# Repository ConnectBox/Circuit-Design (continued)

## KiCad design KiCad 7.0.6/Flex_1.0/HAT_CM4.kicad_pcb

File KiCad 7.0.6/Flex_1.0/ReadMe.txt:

Re: Saving project with new name (ie file names change)

From: https://forum.kicad.info/t/how-to-clone-a-project/3878/12

--------------------
I did an experiment to see the minimum set of files I needed to rebuild a design. Here they are:

myproj.pro : The project file that ties everything together.
myproj.sch : The Schematic file (or files in the case of a hierarchical design).
myproj.kicad_pcb : The PCB layout. It also contains the footprint for every component used in the PCB layout.
myproj-cache.lib : This contains the schematic symbol for every component used in the schematic file. It gets generated whenever you save the schematic or project.

So all you need are those four files. If the shared libraries with the component footprints and/or schematic symbols are missing, then KiCad seems to get the information it needs from these files. These files may also be given priority even if the shared libraries are present; I don’t know.
-------------------

(NOTE: In KiCAD 5.99 the myproj-cache.lib file is missing... but it doesn't seem to be needed as saving the other files in a new folder and opening the project with KiCAD seems to work fine. There is a file "fp-info-cache" that I DIDN'T copy into the new project directory... but KiCAD seems to have created a new fp-info-cache when I opened the project.) 

From that same link we get the following on using the tool "git":

------------------
You probably don’t want to hear this (most people don’t), but git easily does this for you. (Note that I’m talking about git, not Github.)

In your kicad project directory, just do git init. This creates a repository that stores all your project versions.

Add the project files you want to keep track of. For kicad, there’s really only three you need: git add myproj.pro myproj.sch myproj.kicad_pcb.

Store the current state of your project: git commit -a -m "Some message about this version".

That’s all you need to do to setup versioning. Then whenever you have a version you want to save, run the command git commit -a -m "A message about this version". If you also want to give the snapshot an easy-to-remember name, you can use the command git tag my_version_tag. Then if you ever want to return to that version, use the command git checkout my_version_tag. And if you want to see the history of your project, use git log.
-----------------

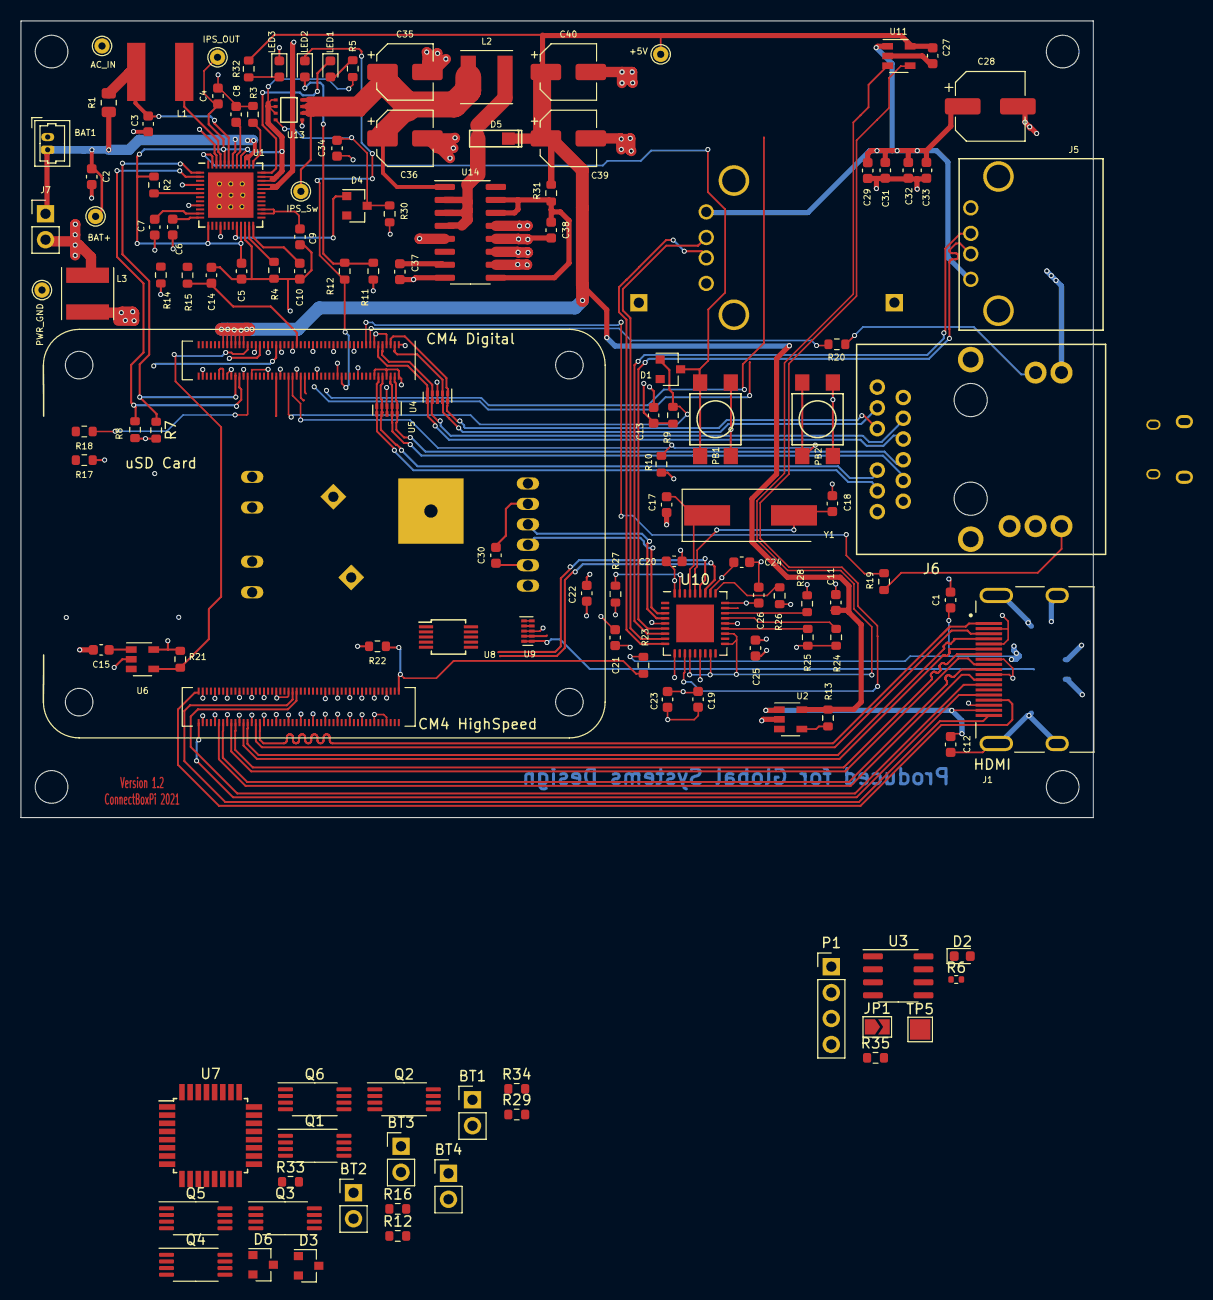
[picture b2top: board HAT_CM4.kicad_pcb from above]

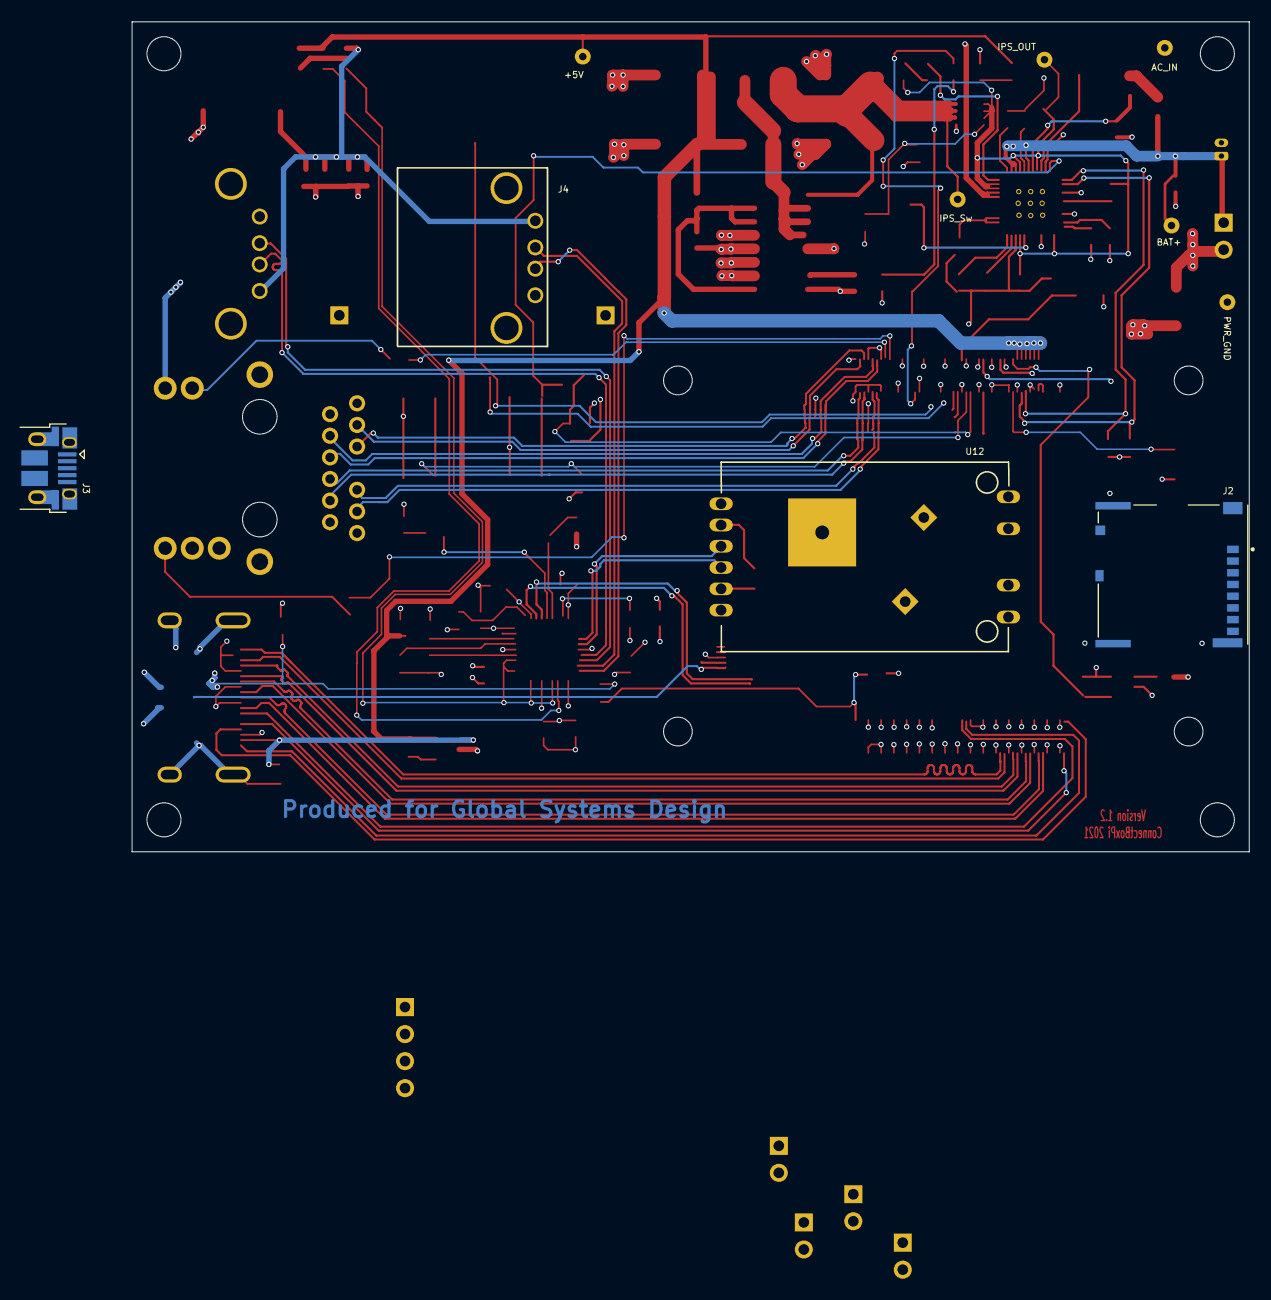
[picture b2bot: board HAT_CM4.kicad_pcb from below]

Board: 4 copper layers, 105.0 x 78.0 mm, 132 parts (4 on the bottom side), 115 nets.

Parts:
BAT1: Molex PicoBlade 53047-0210; Molex PicoBlade 53047-0210 - (swapped pins)
BT1, BT2, BT3, BT4: Battery_Cell; PinHeader_1x02_P2.54mm_Vertical
C1, C30, C34: 22uF; C_0603_1608Metric
C2, C3, C4, C5, C14, C15, C19, C20, C27, C29, C31, C32, C33: 10uF; C_0603_1608Metric
C6, C7, C8: 4.7uF; C_0603_1608Metric
C9, C10, C13: 1uF; C_0603_1608Metric
C11, C12, C21, C22, C23, C24, C25, C26, C38: 0.1uf; C_0603_1608Metric
C17, C18: 27pF; C_0603_1608Metric
C28: 100uF; CP_Elec_6.3x4.5
C35, C36, C39, C40: 150uf; CP_Elec_5x3
C37: 0.22uf; C_0603_1608Metric
D1, D3, D4, D6: MMBD914; D_SOT-23_ANK
D2: LED Green; LED_0603_1608Metric
D5: NRVTS260ESFT1G; SOD-123FL
J1: 690-019-298-412; EDAC 690-019-298-412
J2: Micro_SD_Card_Det; SDCARD_MOLEX_503398-1892
J3: USB_OTG; USB_Micro-B_EDAC_UCON00686
J4, J5: USB_A
J6: MagJack-L829-1J1T-JM; MagJack L829-1J1T-JM
J7: Conn_01x02_Female; PinHeader_1x02_P2.54mm_Vertical
JP1: SolderJumper_2_Open; SolderJumper-2_P1.3mm_Open_TrianglePad1.0x1.5mm
L1: 4.7 uH; INDUCTOR_SMD_6x6-1
L2: 1.0 uH; L_Taiyo-Yuden_MD-5050
L3: 1.5 uH; L_Taiyo-Yuden_NR-50xx
LED1: Red; LED_0603_1608Metric
LED2: Amber; LED_0603_1608Metric
LED3: Green; LED_0603_1608Metric
Module1: ComputeModule4; Raspberry-Pi-4-Compute-Module
P1: Conn_01x04; PinHeader_1x04_P2.54mm_Vertical
PB1, PB2: SPST-PUSH; SW-TL3305
Q1, Q2, Q3, Q4, Q5, Q6: 8205A; TSSOP-8_4.4x3mm_P0.65mm
R1: 0.03 ohm; R_0805_2012Metric
R2, R9, R10, R12, R29, R34, R35: 10K; R_0603_1608Metric
R3: 100; R_0603_1608Metric
R4: 200K; R_0603_1608Metric
R5: 1.8K; R_0603_1608Metric
R6: 1k; R_0402_1005Metric
R7, R8, R16, R22, R23, R33: 2.2K; R_0603_1608Metric
R11, R12#2, R15, R32: 1K; R_0603_1608Metric
R13, R21, R27: 12K; R_0603_1608Metric
R14: 51K; R_0603_1608Metric
R17, R18: nf; R_0603_1608Metric
R19, R20: 470; R_0603_1608Metric
R24, R25, R26, R28: 36.0K; R_0603_1608Metric
R30: 220K; R_0603_1608Metric
R31: 2.0; R_0603_1608Metric
TP1: Pwr_Gnd; TestPoint_THTPad_D1.5mm_Drill0.7mm
TP2: AC_IN; TestPoint_THTPad_D1.5mm_Drill0.7mm
TP3: Bat+; TestPoint_THTPad_D1.5mm_Drill0.7mm
TP4: IPS; TestPoint_THTPad_D1.5mm_Drill0.7mm
TP5: TestPoint; TestPoint_Pad_2.0x2.0mm
TP7: IPS_Sw; TestPoint_THTPad_D1.5mm_Drill0.7mm
TP8: 5V; TestPoint_THTPad_D1.5mm_Drill0.7mm
U1: AXP209; UQFN-48-1EP_6x6mm_Pitch0.4mm_75
U2: RT9742SNGV; SOT-23-5
U3: AT24CS01-SSHM; SOIC-8_3.9x4.9mm_P1.27mm
U4, U5, U9: TPD4EUSB30; USON-10_2.5x1.0mm_P0.5mm
U6, U11: RT9742ANGJ5F; SOT-23-5
U7: ATtiny88-AU; TQFP-32_7x7mm_P0.8mm
U8: FSUSB42MUX; MSOP-10_3x3mm_P0.5mm
U10: USB2514B-I/M2; QFN-36-1EP_6x6mm_P0.5mm_EP3.7x3.7mm
U12: HC-R8812AF1; HC-R8812AU2-th-1
U13: DML10M8LDS-13
U14: MAX1709ESE; SOP-16_3.9x9.9mm_P1.27mm
Y1: 24MHz; Crystal_SMD_HC49-SD

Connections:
+3.3v: C13.1, C19.1, C20.1, C21.1, C22.1, C23.1, C24.1, C25.1, C26.1, C30.1, J6.14 (LEDY_A), J6.16 (COM), Module1.78 (GPIO_VREF(1.8v/3.3v_Input)), Module1.84 (+3.3v_(Output)), Module1.86 (+3.3v_(Output)), R7.2, R8.2, R9.2, R10.2, R11.1, R14.1, R17.1, R21.2, U6.5 (VIN), U8.1 (VCC), U10.5 (VDDA33), U10.10 (VDDA33), U10.15 (VDD33), U10.23 (VDD33), U10.27 (VBUS_DET), U10.29 (VDDA33), U10.36 (VDDA33), U12.1 (PDN), U12.2 (3.3V)
+5v: C11.1, C27.1, C39.1, C40.1, D2.2 (A), D5.1 (K), D6.2 (A), JP1.1 (A), Module1.77 (+5v_(Input)), Module1.79 (+5v_(Input)), Module1.81 (+5v_(Input)), Module1.83 (+5v_(Input)), Module1.85 (+5v_(Input)), Module1.87 (+5v_(Input)), P1.2, R12.2, R13.2, R31.1, R32.1, TP8.1, U2.5 (VIN), U3.8 (VCC), U11.5 (VIN)
/BatteryModule1/ADC0: R29.1, R33.1, U7.23 (PC0)
/BatteryModule1/ADC1: Q4.1 (D), Q4.8 (D), Q6.1 (D), Q6.8 (D), R33.2, U7.24 (PC1)
/BatteryModule1/ADC2: R12.1, R16.1, U7.25 (PC2)
/BatteryModule1/BT1_ENA: Q2.4 (G1), Q2.5 (G2), R34.1, U7.12 (PB0)
/BatteryModule1/BT1_RD: Q4.4 (G1), U7.30 (PD0)
/BatteryModule1/BT2_ENA: Q3.4 (G1), Q3.5 (G2), U7.13 (PB1)
/BatteryModule1/BT2_RD: Q4.5 (G2), U7.31 (PD1)
/BatteryModule1/BT3_ENA: Q1.4 (G1), Q1.5 (G2), U7.14 (PB2)
/BatteryModule1/BT3_RD: Q6.4 (G1), U7.32 (PD2)
/BatteryModule1/BT4_ENA: Q5.4 (G1), Q5.5 (G2), U7.7 (PB6)
/BatteryModule1/BT4_RD: Q6.5 (G2), U7.1 (PD3)
/BatteryModule1/I2C_SCL: Module1.80 (SCL0), P1.3, R8.1, U1.2 (SCK), U3.6 (SCL), U7.28 (PC5)
/BatteryModule1/I2C_SDA: Module1.82 (SDA0), P1.4, R7.1, U1.1 (SDA), U3.5 (SDA), U7.27 (PC4)
/CM4_GPIO/+1.8v: Module1.88 (+1.8v_(Output)), Module1.90 (+1.8v_(Output))
/CM4_GPIO/ETH_LEDG: Module1.17 (Ethernet_nLED2(3.3v)), R19.1
/CM4_GPIO/ETH_LEDY: Module1.15 (Ethernet_nLED3(3.3v)), R20.1
/CM4_GPIO/EXT_ENA: D4.2 (A), R14.2, R15.2, U1.20 (EXTEN)
/CM4_GPIO/GPIO6: LED2.1 (K), Module1.30 (GPIO6), R12#2.2
/CM4_GPIO/GPIO_IRQ: C14.1, Module1.51 (GPIO15), R15.1
/CM4_GPIO/GPIO_PB1: D1.2 (A), Module1.56 (GPIO3), R9.1
/CM4_GPIO/GPIO_PB2: Module1.54 (GPIO4), PB2.1, R10.1
/CM4_GPIO/PowerSwitch: D1.1 (K), PB1.1, U1.47 (PwrON)
/CM4_GPIO/Reserved: Module1.76 (Reserved), R18.1
/CM4_GPIO/SD_CLK: J2.5 (CLK), Module1.57 (SD_CLK)
/CM4_GPIO/SD_CMD: J2.3 (CMD), Module1.62 (SD_CMD)
/CM4_GPIO/SD_DAT0: J2.7 (DAT0), Module1.63 (SD_DAT0)
/CM4_GPIO/SD_DAT1: J2.8 (DAT1), Module1.67 (SD_DAT1)
/CM4_GPIO/SD_DAT2: J2.1 (DAT2), Module1.69 (SD_DAT2)
/CM4_GPIO/SD_DAT3: J2.2 (DAT3/CD), Module1.61 (SD_DAT3)
/CM4_GPIO/SD_PWR: C15.1, J2.4 (VDD), U6.1 (VOUT)
/CM4_GPIO/SD_PWR_ON: Module1.75 (SD_PWR_ON), R21.1, U6.4 (EN)
/CM4_GPIO/TRD0_N: J6.10 (TRD0-), Module1.10 (Ethernet_Pair0_N), U5.4 (D2+), U5.7
/CM4_GPIO/TRD0_P: J6.11 (TRD0+), Module1.12 (Ethernet_Pair0_P), U5.5 (D2-), U5.6
/CM4_GPIO/TRD1_N: J6.5 (TRD1-), Module1.6 (Ethernet_Pair1_N), U5.2 (D1-), U5.9
/CM4_GPIO/TRD1_P: J6.4 (TRD1+), Module1.4 (Ethernet_Pair1_P), U5.1 (D1+), U5.10
/CM4_GPIO/TRD2_N: J6.2 (TRD2-), Module1.9 (Ethernet_Pair2_N), U4.4 (D2+), U4.7
/CM4_GPIO/TRD2_P: J6.3 (TRD2+), Module1.11 (Ethernet_Pair2_P), U4.5 (D2-), U4.6
/CM4_GPIO/TRD3_N: J6.9 (TRD3-), Module1.5 (Ethernet_Pair3_N), U4.1 (D1+), U4.10
/CM4_GPIO/TRD3_P: J6.8 (TRD3+), Module1.3 (Ethernet_Pair3_P), U4.2 (D1-), U4.9
/CM4_HighSpeed/HDMI0_CEC: J1.13 (CEC), Module1.151 (HDMI0_CEC)
/CM4_HighSpeed/HDMI0_CK_N: J1.12 (CK-), Module1.190 (HDMI0_CLK_N)
/CM4_HighSpeed/HDMI0_CK_P: J1.10 (CK+), Module1.188 (HDMI0_CLK_P)
/CM4_HighSpeed/HDMI0_D0_N: J1.9 (D0-), Module1.184 (HDMI0_TX0_N)
/CM4_HighSpeed/HDMI0_D0_P: J1.7 (D0+), Module1.182 (HDMI0_TX0_P)
/CM4_HighSpeed/HDMI0_D1_N: J1.6 (D1-), Module1.178 (HDMI0_TX1_N)
/CM4_HighSpeed/HDMI0_D1_P: J1.4 (D1+), Module1.176 (HDMI0_TX1_P)
/CM4_HighSpeed/HDMI0_D2_N: J1.3 (D2-), Module1.172 (HDMI0_TX2_N)
/CM4_HighSpeed/HDMI0_D2_P: J1.1 (D2+), Module1.170 (HDMI0_TX2_P)
/CM4_HighSpeed/HDMI0_HOTPLUG: J1.19 (HPD/HEAC-), Module1.153 (HDMI0_HOTPLUG)
/CM4_HighSpeed/HDMI0_SCL: J1.15 (SCL), Module1.200 (HDMI0_SCL)
/CM4_HighSpeed/HDMI0_SDA: J1.16 (SDA), Module1.199 (HDMI0_SDA)
/CM4_HighSpeed/HDMI_5v: C12.1, J1.18 (+5V), U2.1 (VOUT)
/CM4_HighSpeed/USB2_N: Module1.103 (USB2_N), U8.4 (D_N)
/CM4_HighSpeed/USB2_P: Module1.105 (USB2_P), U8.3 (D_P)
/CM4_HighSpeed/USBOTG_ID: Module1.101 (USB_OTG_ID), R22.1, R23.2, U8.2 (SEL)
/Charge control/BAT+: BAT1.1, BT1.1 (+), BT2.1 (+), BT3.1 (+), BT4.1 (+), C2.1, J7.1, R1.1, R29.2, R34.2, TP3.1, U1.38 (Batt), U1.39 (Batt), U1.42 (BatSense)
/Charge control/IPS_OUT: C4.1, C5.1, R2.2, R5.1, TP4.1, U1.13 (LDO_24_In), U1.21 (APS), U1.34 (IPS_Out), U1.35 (IPS_Out), U1.40 (LDO_3_In), U1.44 (Vin_1), U13.1 (IN), U13.2 (IN), U13.3 (VBias)
/USB Hub/HD2_N: U10.3 (USBDM_DN2/PRT_DIS_M2), U12.3 (DM-)
/USB Hub/HD2_P: U10.4 (USBDP_DN2/PRT_DIS_P2), U12.4 (DP+)
/USB Hub/HD3_N: J5.2 (D-), U10.6 (USBDM_DN3/PRT_DIS_M3)
/USB Hub/HD3_P: J5.3 (D+), U10.7 (USBDP_DN3/PRT_DIS_P3)
/USB Hub/HD4_N: J4.2 (D-), U10.8 (USBDM_DN4/PRT_DIS_M4)
/USB Hub/HD4_P: J4.3 (D+), U10.9 (USBDP_DN4/PRT_DIS_P4)
/USB Hub/PWR1: U10.12 (PRTPWR1/BC_EN1), U11.4 (EN)
/USB Hub/USBD_N: J3.2 (D-), U8.8 (HSD1_M), U9.4 (D2+), U9.7
/USB Hub/USBD_P: J3.3 (D+), U8.9 (HSD1_P), U9.5 (D2-), U9.6
/USB Hub/USBH_N: U8.6 (HSD0_M), U10.30 (USBDM_UP)
/USB Hub/USBH_P: U8.7 (HSD0_P), U10.31 (USBDP_UP)
/USB Hub/VBUS: C28.1, C29.1, C31.1, C32.1, C33.1, J4.1 (VBUS), J5.1 (VBUS), U11.1 (VOUT)
/USB Hub/nOCS1: U10.13 (OCS_N1), U10.17 (OCS_N2), U10.19 (OCS_N3), U10.21 (OCS_N4), U11.3 (/FLG)
AC_IN: C1.1, D3.2 (A), J3.1 (VBUS), R23.1, TP2.1, U1.32 (AC_IN), U1.33 (AC_IN)
GND: C1.2, C5.2, C9.1, C10.1, C11.2, C12.2, C13.2, C14.2, C15.2, C17.2, C18.2, C19.2, C20.2, C21.2, C22.2, C23.2, C24.2, C25.2, C26.2, C27.2, C28.2, C29.2, C30.2, C31.2, C32.2, C33.2, J1.2 (D2S), J1.5 (D1S), J1.8 (D0S), J1.11 (CKS), J1.17 (GND), J1.SH1 (SH), J1.SH2 (SH), J1.SH3 (SH), J1.SH4 (SH), J2.6 (VSS), J2.11 (SHIELD), J3.5 (GND), J3.6 (Shield), J4.4 (GND), J4.5 (Shield), J5.4 (GND), J5.5 (Shield), J6.18 (SHIELD), L3.2, Module1.1 (GND), Module1.2 (GND), Module1.7 (GND), Module1.8 (GND), Module1.13 (GND), Module1.14 (GND), Module1.22 (GND), Module1.23 (GND), Module1.32 (GND), Module1.33 (GND), Module1.42 (GND), Module1.43 (GND), Module1.52 (GND), Module1.53 (GND), Module1.59 (GND), Module1.60 (GND), Module1.65 (GND), Module1.66 (GND), Module1.71 (GND), Module1.74 (GND), Module1.98 (GND), Module1.107 (GND), Module1.108 (GND), Module1.113 (GND), Module1.114 (GND), Module1.119 (GND), Module1.120 (GND), Module1.125 (GND), Module1.126 (GND), Module1.131 (GND), Module1.132 (GND), Module1.137 (GND), Module1.138 (GND), Module1.144 (GND), Module1.150 (GND), Module1.155 (GND), Module1.156 (GND), Module1.161 (GND), Module1.162 (GND), Module1.167 (GND), Module1.168 (GND), Module1.173 (GND), Module1.174 (GND), Module1.179 (GND), Module1.180 (GND), Module1.185 (GND), Module1.186 (GND), Module1.191 (GND), Module1.192 (GND), Module1.197 (GND), Module1.198 (GND), P1.1, PB1.2, PB2.2, Q1.6 (S2), Q1.7 (S2), Q2.6 (S2), Q2.7 (S2), Q3.6 (S2), Q3.7 (S2), Q5.6 (S2), Q5.7 (S2), R4.1, R16.2, R22.2, R24.2, R25.2, R26.2, R27.1, R28.2, R35.1, U1.22 (A_Gnd), U2.2 (GND), U3.1 (A0), U3.2 (A1), U3.3 (A2), U3.4 (GND), U4.3 (GND), U4.8 (GND), U5.3 (GND), U5.8 (GND), U6.2 (GND), U7.5 (GND), U7.21 (GND), U8.5 (GND), U8.10 (nOE), U9.3 (GND), U9.8 (GND), U10.37 (VSS), U11.2 (GND), U12.5 (GND), U12.7 (GND), U12.9 (GND), U12.10 (GND), U12.12 (GND), U12.13 (GND), U12.14 (GND), U12.15 (GND)
unnamed: BT1.2 (-), Q2.2 (S1), Q2.3 (S1), Q4.2 (S1), Q4.3 (S1)
unnamed: BT2.2 (-), Q3.2 (S1), Q3.3 (S1), Q4.6 (S2), Q4.7 (S2)
unnamed: BT3.2 (-), Q1.2 (S1), Q1.3 (S1), Q6.2 (S1), Q6.3 (S1)
unnamed: BT4.2 (-), Q5.2 (S1), Q5.3 (S1), Q6.6 (S2), Q6.7 (S2)
unnamed: C3.1, L1.1, R1.2, U1.43 (ChgSense)
unnamed: C6.2, U1.12 (LDO_2)
unnamed: C7.2, U1.11 (LDO_4)
unnamed: C8.2, U1.41 (LDO_3)
unnamed: C9.2, U1.26 (V_Internal), U1.27 (LDO_1_Set)
unnamed: C10.2, U1.24 (V_Ref)
unnamed: C17.1, U10.33 (XTALIN/CLKIN), Y1.1
unnamed: C18.1, U10.32 (XTALOUT), Y1.2
unnamed: C34.1, D4.1 (K), R30.1, U13.4 (ON)
unnamed: C35.1, C36.1, L2.1, TP7.1, U13.6 (OUT), U13.7 (OUT), U13.8 (OUT), U14.1 (ONA)
unnamed: C37.1, U14.7 (REF)
unnamed: C38.1, R31.2, U14.9 (OUT), U14.14 (_3.3/5), U14.15 (CLK)
unnamed: D2.1 (K), R6.1, TP5.1
unnamed: D3.1 (K), D6.1 (K), U7.4 (VCC), U7.18 (AVCC)
unnamed: D5.2 (A), L2.2, U14.2 (LX), U14.3 (LX), U14.4 (LX)
unnamed: J2.9 (DET_B), R18.2
unnamed: J2.10 (DET_A), R17.2
unnamed: J6.13 (LEDY_K), R20.2
unnamed: J6.17 (LEDG_K), R19.2
unnamed: JP1.2 (B), R35.2, U3.7 (WP)
unnamed: L1.2, U1.45 (LX1)
unnamed: LED1.1 (K), U1.36 (ChgLED)
unnamed: LED1.2 (A), R5.2
unnamed: LED2.2 (A), R11.2, R12#2.1
unnamed: LED3.2 (A), R32.2
unnamed: R2.1, U1.6 (N_VBus_En)
unnamed: R3.1, U1.37 (TS)
unnamed: R4.2, U1.23 (Bias)
unnamed: R13.1, U2.4 (EN)
unnamed: R24.1, U10.24 (SCL/SMBCLK/CFG_SEL0)
unnamed: R25.1, U10.22 (SDA/SMBDATA/NON_REM1)
unnamed: R26.1, U10.28 (SUSP_IND/LOCAL_PWR/NON_REM0)
unnamed: R27.2, U10.35 (RBIAS)
unnamed: R28.1, U10.25 (HS_IND/CFG_SEL1)
unnamed: U9.1 (D1+), U9.10
unnamed: U9.2 (D1-), U9.9
PWR_GND: BAT1.2, C2.2, C3.2, C4.2, C6.1, C7.1, C8.1, C34.2, C35.2, C36.2, C37.2, C38.2, C39.2, C40.2, J7.2, L3.1, LED3.1 (K), R3.2, R30.2, TP1.1, U1.4 (N_OE), U1.9 (PGnd_2), U1.16 (PGnd_3), U1.46 (PGnd_1), U1.49 (GND_PAD), U13.5 (GND), U14.5 (GND), U14.8 (GND), U14.10 (FB), U14.11 (PGND), U14.12 (PGND), U14.13 (PGND)
